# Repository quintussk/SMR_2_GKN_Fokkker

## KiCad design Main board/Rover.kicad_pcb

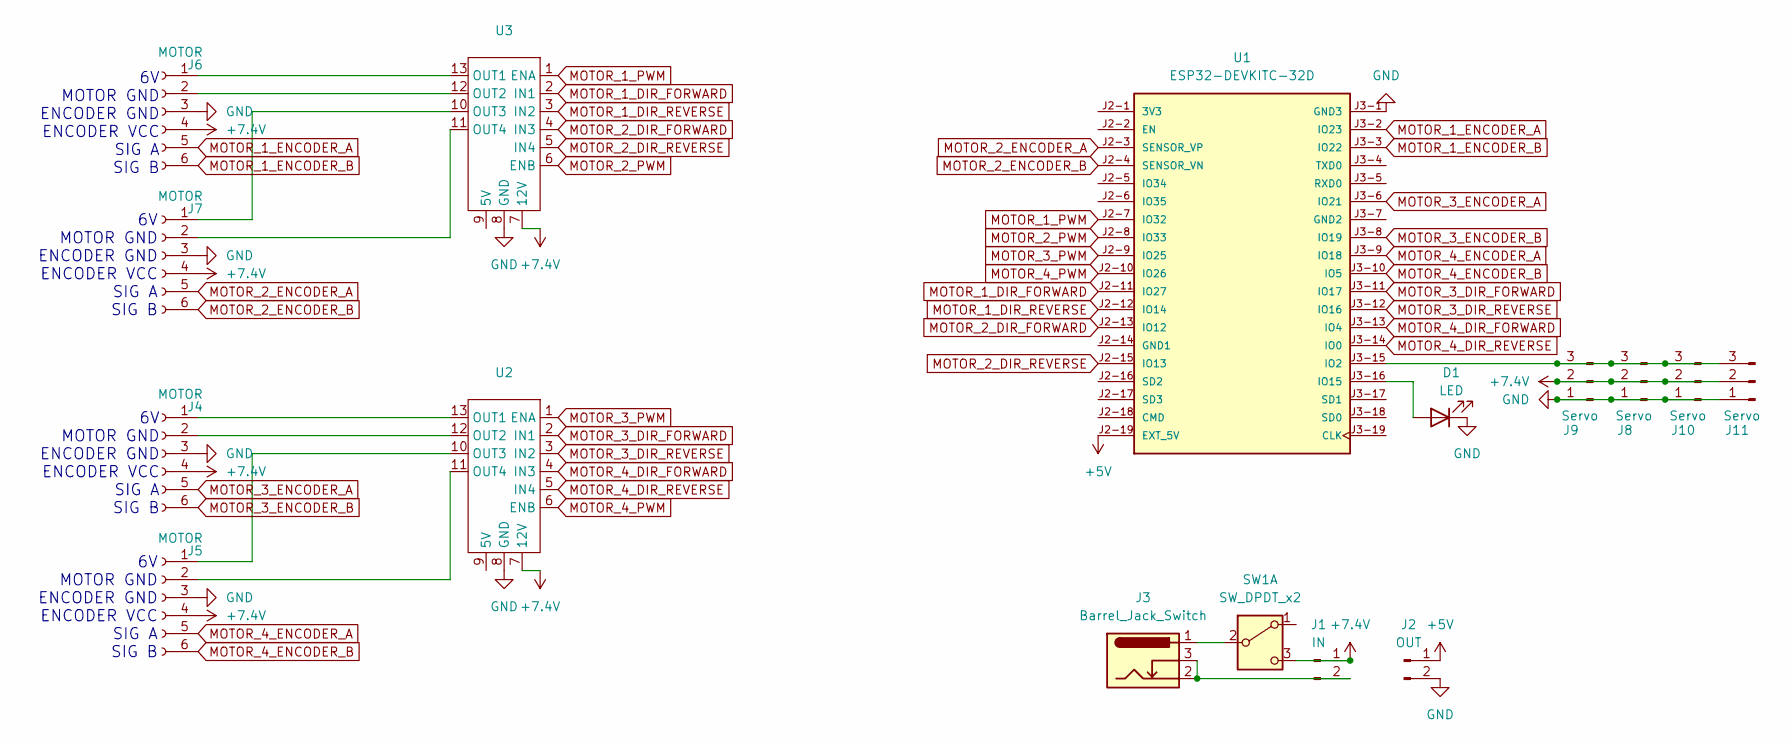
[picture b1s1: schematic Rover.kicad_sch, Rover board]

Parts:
D1: LED; LED_D5.0mm_Clear
J1: IN; SolderWire-0.75sqmm_1x02_P4.8mm_D1.25mm_OD2.3mm
J2: OUT; SolderWire-0.75sqmm_1x02_P4.8mm_D1.25mm_OD2.3mm
J3: Barrel_Jack_Switch; BarrelJack_Horizontal
J4, J5, J6, J7: MOTOR; PinHeader_1x06_P2.54mm_Vertical
J8, J9, J10, J11: Servo; PinHeader_1x03_P2.54mm_Vertical
SW1: SW_DPDT_x2; SW_E-Switch_EG2219_DPDT_Angled
U1: ESP32-DEVKITC-32D; MODULE_ESP32-DEVKITC-32D; PARTREV V4
U2, U3: L298N

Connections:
+5V: J2.1, U1.J2-19 (EXT_5V)
+7.4V: J1.1, J4.4, J5.4, J6.4, J7.4, J8.2, J9.2, J10.2, J11.2, SW1.3 (C), U2.7 (12V), U3.7 (12V)
GND: D1.1 (K), J2.2, J4.3, J5.3, J6.3, J7.3, J8.1, J9.1, J10.1, J11.1, U1.J3-1 (GND3), U2.8 (GND), U3.8 (GND)
MOTOR_1_DIR_FORWARD: U1.J2-11 (IO27), U3.2 (IN1)
MOTOR_1_DIR_REVERSE: U1.J2-12 (IO14), U3.3 (IN2)
MOTOR_1_ENCODER_A: J6.5, U1.J3-2 (IO23)
MOTOR_1_ENCODER_B: J6.6, U1.J3-3 (IO22)
MOTOR_1_PWM: U1.J2-7 (IO32), U3.1 (ENA)
MOTOR_2_DIR_FORWARD: U1.J2-13 (IO12), U3.4 (IN3)
MOTOR_2_DIR_REVERSE: U1.J2-15 (IO13), U3.5 (IN4)
MOTOR_2_ENCODER_A: J7.5, U1.J2-3 (SENSOR_VP)
MOTOR_2_ENCODER_B: J7.6, U1.J2-4 (SENSOR_VN)
MOTOR_2_PWM: U1.J2-8 (IO33), U3.6 (ENB)
MOTOR_3_DIR_FORWARD: U1.J3-11 (IO17), U2.2 (IN1)
MOTOR_3_DIR_REVERSE: U1.J3-12 (IO16), U2.3 (IN2)
MOTOR_3_ENCODER_A: J4.5, U1.J3-6 (IO21)
MOTOR_3_ENCODER_B: J4.6, U1.J3-8 (IO19)
MOTOR_3_PWM: U1.J2-9 (IO25), U2.1 (ENA)
MOTOR_4_DIR_FORWARD: U1.J3-13 (IO4), U2.4 (IN3)
MOTOR_4_DIR_REVERSE: U1.J3-14 (IO0), U2.5 (IN4)
MOTOR_4_ENCODER_A: J5.5, U1.J3-9 (IO18)
MOTOR_4_ENCODER_B: J5.6, U1.J3-10 (IO5)
MOTOR_4_PWM: U1.J2-10 (IO26), U2.6 (ENB)
unnamed: D1.2 (A), U1.J3-16 (IO15)
unnamed: J1.2, J3.2, J3.3
unnamed: J4.1, U2.13 (OUT1)
unnamed: J4.2, U2.12 (OUT2)
unnamed: J5.1, U2.10 (OUT3)
unnamed: J5.2, U2.11 (OUT4)
unnamed: J6.1, U3.13 (OUT1)
unnamed: J6.2, U3.12 (OUT2)
unnamed: J7.1, U3.10 (OUT3)
unnamed: J7.2, U3.11 (OUT4)
unnamed: J8.3, J9.3, J10.3, J11.3, U1.J3-15 (IO2)
unnamed: J3.1, SW1.2 (B)

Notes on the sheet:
6V MOTOR GND ENCODER GND ENCODER VCC SIG A SIG B

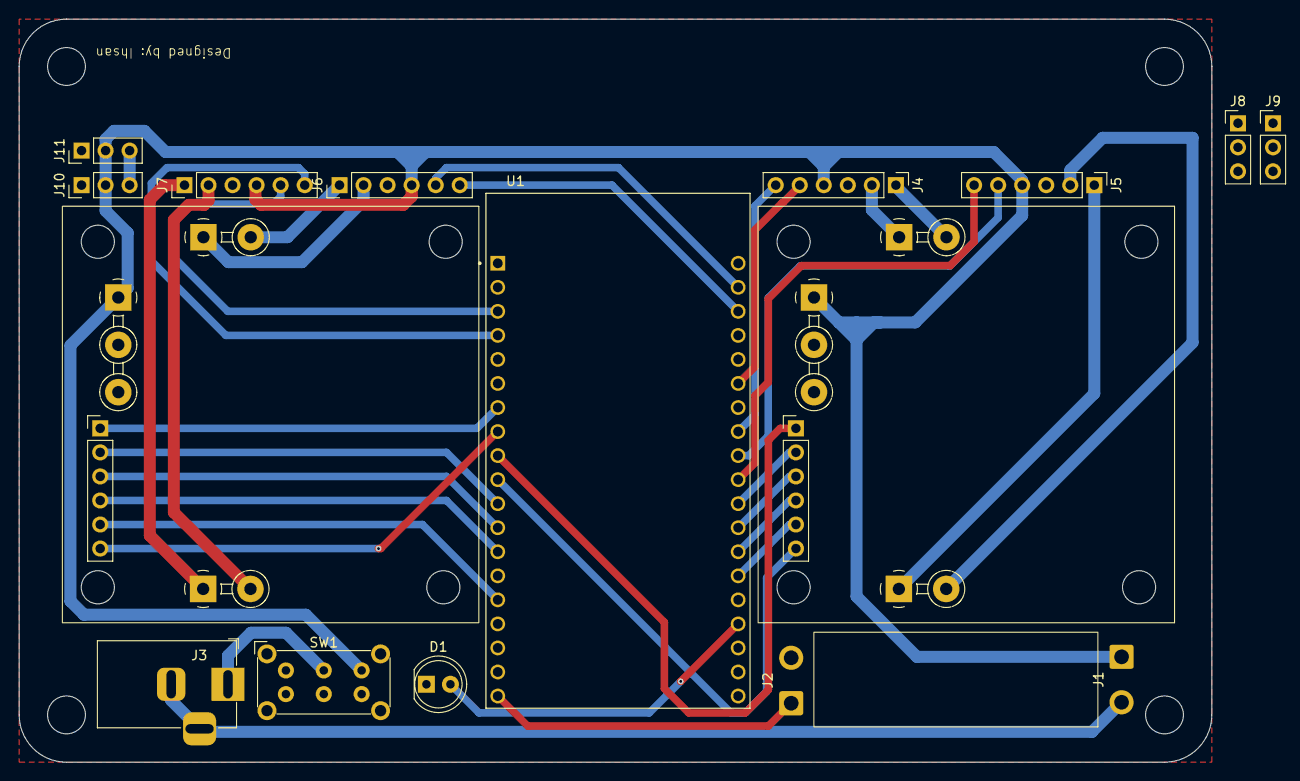
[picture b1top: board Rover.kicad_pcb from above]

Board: 2 copper layers, 126.0 x 78.5 mm, 16 parts (0 on the bottom side), 35 nets.

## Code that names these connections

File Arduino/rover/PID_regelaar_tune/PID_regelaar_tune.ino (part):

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
#define LED_PIN 15
// Pin definitions
#define MOTOR_1_PWM 32
#define MOTOR_1_DIR_FORWARD 27
#define MOTOR_1_DIR_REVERSE 14
#define MOTOR_1_ENCODER_A 23
#define MOTOR_1_ENCODER_B 22

#define MOTOR_2_PWM 33
#define MOTOR_2_DIR_FORWARD 12
#define MOTOR_2_DIR_REVERSE 13
#define MOTOR_2_ENCODER_A 36
#define MOTOR_2_ENCODER_B 39

#define MOTOR_3_PWM 25
#define MOTOR_3_DIR_FORWARD 17
#define MOTOR_3_DIR_REVERSE 16
#define MOTOR_3_ENCODER_A 21
#define MOTOR_3_ENCODER_B 19

#define MOTOR_4_PWM 26
#define MOTOR_4_DIR_FORWARD 4
#define MOTOR_4_DIR_REVERSE 0
#define MOTOR_4_ENCODER_A 18
#define MOTOR_4_ENCODER_B 5

// Node State
enum states {
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    pinMode(LED_PIN, OUTPUT);

    // Initialize motor control pins
    pinMode(MOTOR_1_DIR_FORWARD, OUTPUT);
    pinMode(MOTOR_1_DIR_REVERSE, OUTPUT);
    pinMode(MOTOR_2_DIR_FORWARD, OUTPUT);
    pinMode(MOTOR_2_DIR_REVERSE, OUTPUT);
    pinMode(MOTOR_3_DIR_FORWARD, OUTPUT);
    pinMode(MOTOR_3_DIR_REVERSE, OUTPUT);
    pinMode(MOTOR_4_DIR_FORWARD, OUTPUT);
    pinMode(MOTOR_4_DIR_REVERSE, OUTPUT);

    // Initialize encoder pins
    pinMode(MOTOR_1_ENCODER_A, INPUT_PULLUP);
    pinMode(MOTOR_1_ENCODER_B, INPUT_PULLUP);
    pinMode(MOTOR_2_ENCODER_A, INPUT_PULLUP);
    pinMode(MOTOR_2_ENCODER_B, INPUT_PULLUP);
    pinMode(MOTOR_3_ENCODER_A, INPUT_PULLUP);
    pinMode(MOTOR_3_ENCODER_B, INPUT_PULLUP);
    pinMode(MOTOR_4_ENCODER_A, INPUT_PULLUP);
    pinMode(MOTOR_4_ENCODER_B, INPUT_PULLUP);

    // Attach interrupts for encoders
    attachInterrupt(digitalPinToInterrupt(MOTOR_1_ENCODER_A), encoder_motor1, CHANGE);
    attachInterrupt(digitalPinToInterrupt(MOTOR_2_ENCODER_A), encoder_motor2, CHANGE);
    attachInterrupt(digitalPinToInterrupt(MOTOR_3_ENCODER_A), encoder_motor3, CHANGE);
    attachInterrupt(digitalPinToInterrupt(MOTOR_4_ENCODER_A), encoder_motor4, CHANGE);

    // Initialize PID controllers
    pidMotor1.SetMode(AUTOMATIC);
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
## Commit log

2024-11-26 drawio
2024-11-28 3D model V1
2024-11-30 added main board
2024-12-04 arduino
2024-12-05 chanhed model
2024-12-05 morning
2024-12-09 updated pcb
2024-12-11 message
2024-12-12 detect red blob
2024-12-12 vision
2024-12-13 Create Rover V2
2024-12-13 Create rover step file
2024-12-18 add edge detection
2025-01-08 web app
2025-01-08 raspberrypi update
2025-01-08 raspberrypi update latest
2025-01-08 adding gitnore
2025-01-09 img processing
2025-01-13 added red blob detection
2025-01-13 arduino file
2025-01-16 yolo
2025-01-20 added wiring diagram
2025-01-20 Commit 20-1
2025-01-20 Camera stich commit
2025-01-21 morning 21-jan
2025-01-21 Arduino -- Update
2025-01-21 testing from pi
2025-01-21 arduino code change
2025-01-21 last commit 21-1
2025-01-22 last working - fik stitching
2025-01-22 pictures
2025-01-22 Auto stash before merge of "main" and "origin/main"
2025-01-22 new model
2025-01-22 homing arduino
2025-01-22 Go/No/Go working
2025-01-23 Untested - 23-1
2025-01-23 HTML Changes
2025-01-23 Test Change
2025-01-23 arduino relay
2025-01-23 work in progress
2025-01-23 Workin
2025-01-23 remove numbers
2025-01-23 clear json
2025-01-23 working
2025-01-23 broken code
2025-01-24 last working
2025-01-24 last
2025-01-24 New Best
2025-01-24 fryday
2025-01-27 test camera
2025-01-27 testing camera options
2025-01-27 test scan
2025-01-27 new camera
2025-01-27 before
